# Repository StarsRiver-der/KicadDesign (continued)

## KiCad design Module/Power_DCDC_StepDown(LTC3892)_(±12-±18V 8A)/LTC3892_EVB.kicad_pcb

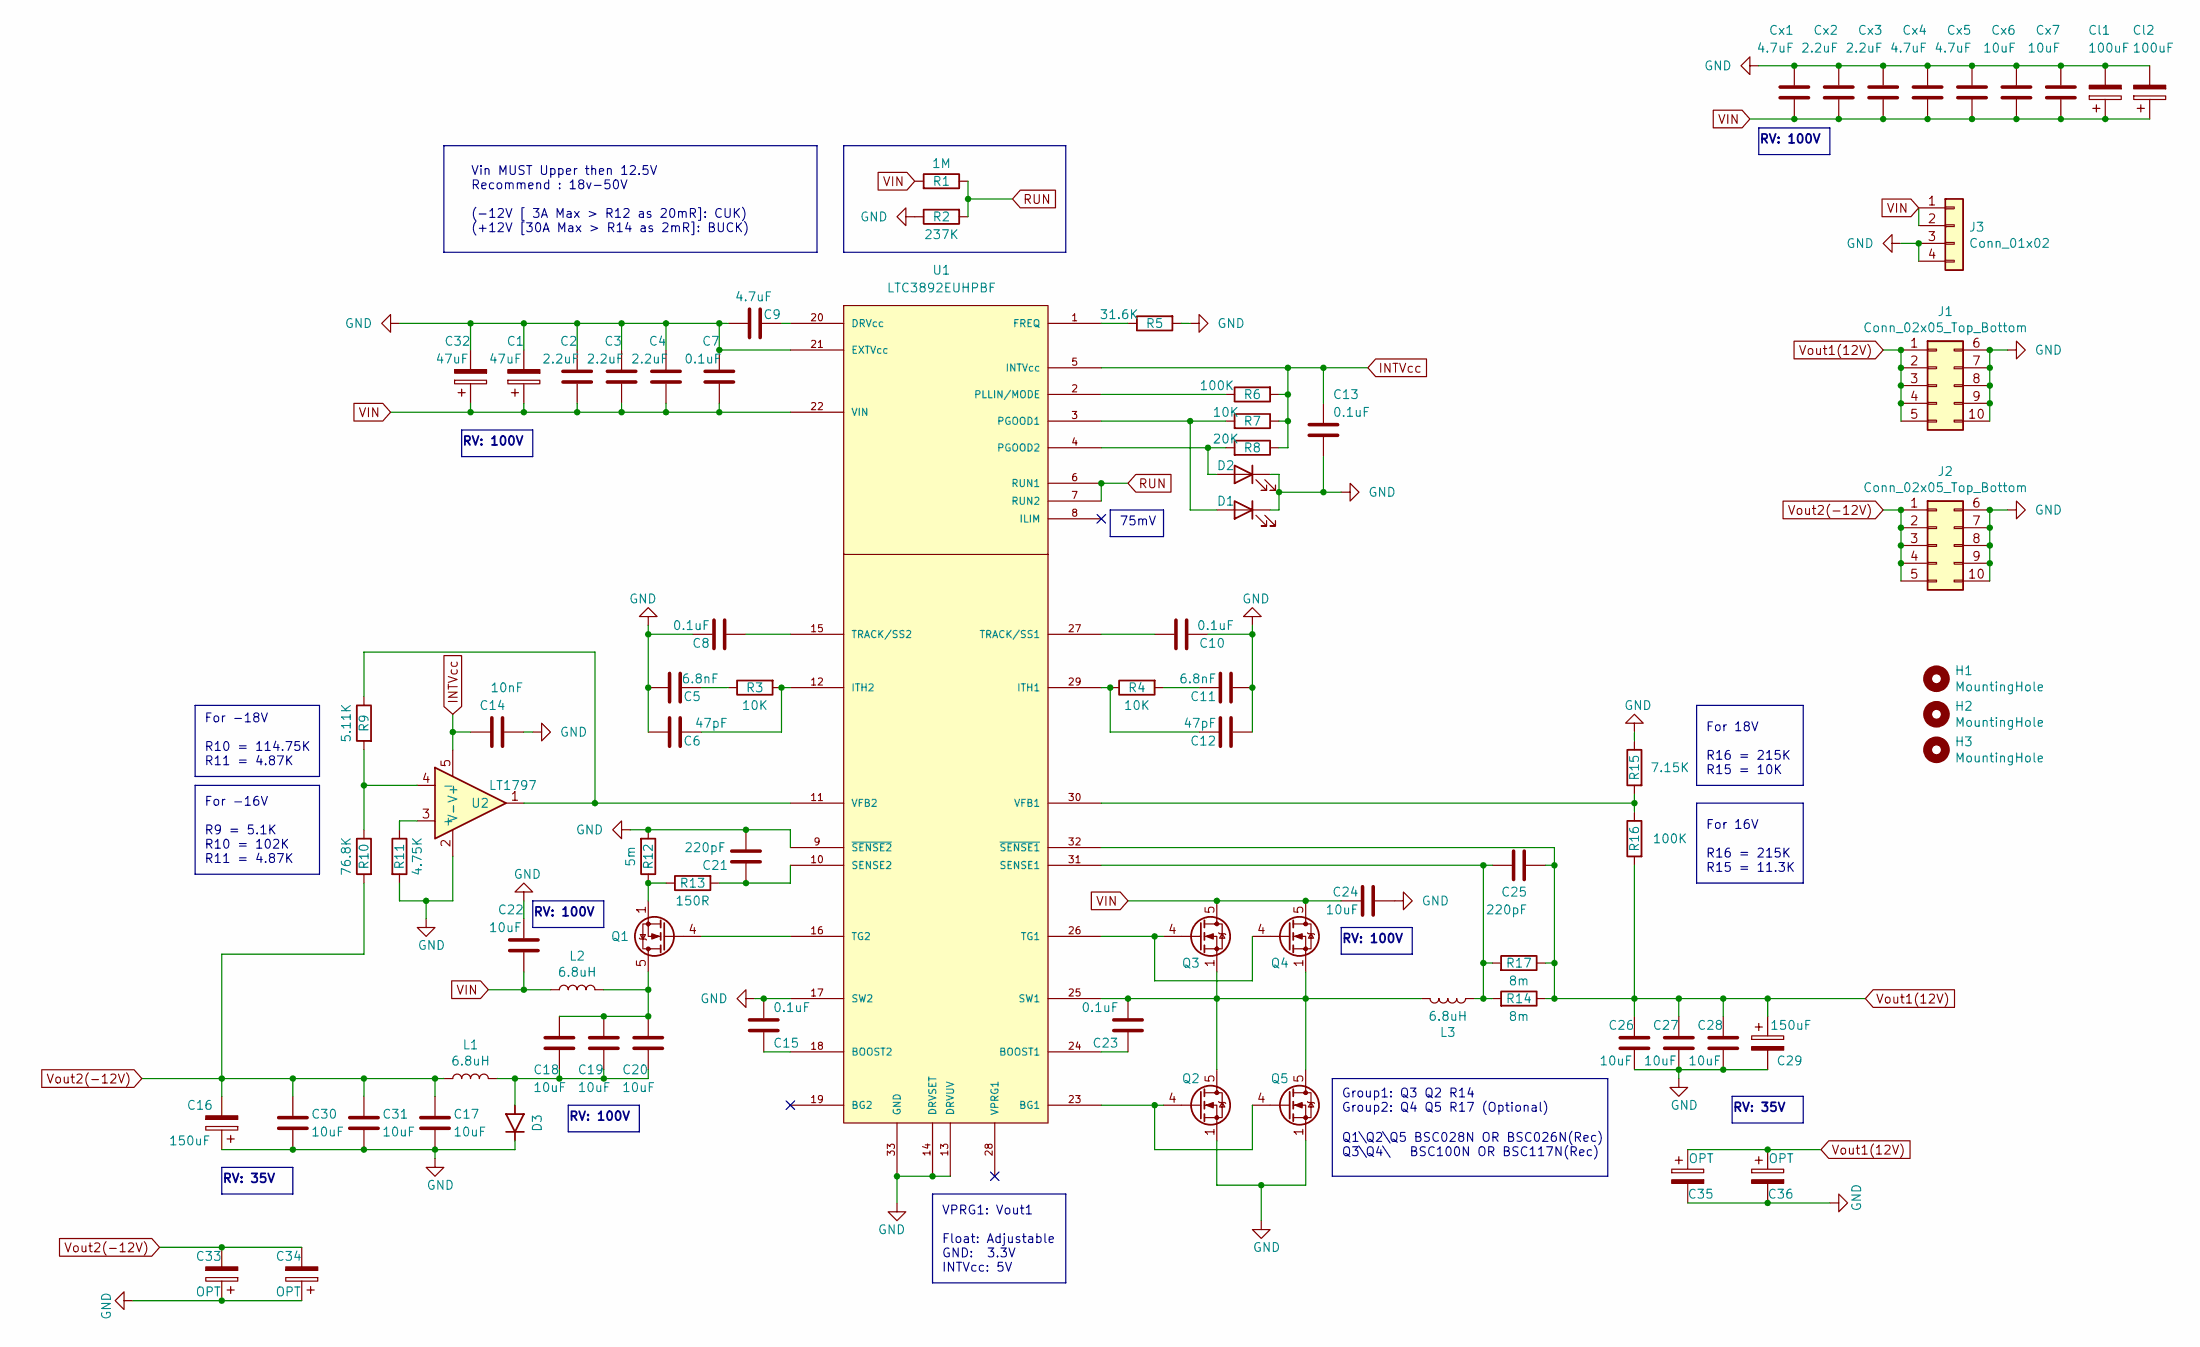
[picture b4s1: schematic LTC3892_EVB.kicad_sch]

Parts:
C1, C32: 47uF; CP_Elec_10x10
C2, C3, C4: 2.2uF; C_1206_3216Metric
C5, C11: 6.8nF; C_0402_1005Metric
C6, C12: 47pF; C_0402_1005Metric
C7, C23: 0.1uF; C_0603_1608Metric
C8, C10, C13, C15: 0.1uF; C_0402_1005Metric
C9: 4.7uF; C_0402_1005Metric
C14: 10nF; C_0402_1005Metric
C16, C29: 150uF; CP_Elec_8x10
C17, C18, C19, C20, C22, C24, C26, C27, C28, C30, C31: 10uF; C_1206_3216Metric
C21, C25: 220pF; C_0402_1005Metric
C33, C34, C35, C36: OPT; CP_Elec_8x10
Cl1, Cl2: 100uF; CP_Elec_10x10
Cx1, Cx4, Cx5: 4.7uF; C_1206_3216Metric
Cx2, Cx3: 2.2uF; C_1206_3216Metric
Cx6, Cx7: 10uF; C_1206_3216Metric
D1, D2: LED; LED_0402_1005Metric
D3: SBR8U60P5-13; DIO_PDS360-13; MPN SBR8U60P5-13
H1, H2, H3: MountingHole; MountingHole_2.2mm_M2
J1, J2: Conn_02x05_Top_Bottom; Molex_Micro-Fit_3.0_43045-1012_2x05_P3.00mm_Vertical
J3: Conn_01x02; Molex_Mini-Fit_Jr_5566-04A_2x02_P4.20mm_Vertical
L1, L2, L3: 6.8uH; L_Wuerth_HCM-1350
Q1, Q2, Q5: BSC026N08NS5; TDSON-8-1
Q3, Q4: BSC117N08NS5; TDSON-8-1
R1: 1M; R_0402_1005Metric
R2: 237K; R_0402_1005Metric
R3, R4, R7: 10K; R_0402_1005Metric
R5: 31.6K; R_0402_1005Metric
R6, R16: 100K; R_0402_1005Metric
R8: 20K; R_0402_1005Metric
R9: 5.11K; R_0402_1005Metric
R10: 76.8K; R_0402_1005Metric
R11: 4.75K; R_0402_1005Metric
R12: 5m; R_2512_6332Metric
R13: 150R; R_0402_1005Metric
R14, R17: 8m; R_2512_6332Metric
R15: 7.15K; R_0402_1005Metric
U1: LTC3892EUHPBF; QFN-32_UH; MANUFACTURER_PART_NUMBER ltc3892euh#pbf
U2: LT1797; SOT-23-5

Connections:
GND: C1.2, C2.2, C3.2, C4.2, C5.1, C6.1, C7.2, C8.1, C9.1, C10.2, C11.2, C12.2, C13.2, C14.2, C15.1, C16.1, C17.1, C21.1, C22.2, C24.2, C26.1, C27.1, C28.1, C29.2, C30.1, C31.1, C32.2, C33.1, C34.1, C35.2, C36.2, Cl1.2, Cl2.2, Cx1.1, Cx2.1, Cx3.1, Cx4.1, Cx5.1, Cx6.1, Cx7.1, D1.1 (K), D2.1 (K), D3.3, J1.6, J1.7, J1.8, J1.9, J1.10, J2.6, J2.7, J2.8, J2.9, J2.10, J3.3, J3.4, Q2.1 (S), Q2.2 (S), Q2.3 (S), Q5.1 (S), Q5.2 (S), Q5.3 (S), R2.1, R5.2, R11.2, R12.2, R15.1, U1.9 (~SENSE2), U1.13 (DRVUV), U1.14 (DRVSET), U1.17 (SW2), U1.21 (EXTVcc), U1.33 (GND), U2.2 (V-)
INTVcc: C13.1, C14.1, R6.2, R7.1, R8.1, U1.5 (INTVcc), U2.5 (V+)
unnamed: C5.2, R3.1
unnamed: C6.2, R3.2, U1.12 (ITH2)
unnamed: C8.2, U1.15 (TRACK/SS2)
unnamed: C9.2, U1.20 (DRVcc)
unnamed: C10.1, U1.27 (TRACK/SS1)
unnamed: C11.1, R4.2
unnamed: C12.1, R4.1, U1.29 (ITH1)
unnamed: C15.2, U1.18 (BOOST2)
unnamed: C18.1, C19.1, C20.1, D3.1, D3.2, L1.2
unnamed: C18.2, C19.2, C20.2, L2.2, Q1.5 (D)
unnamed: C21.2, R13.2, U1.10 (SENSE2)
unnamed: C23.1, L3.1, Q2.5 (D), Q3.1 (S), Q3.2 (S), Q3.3 (S), Q4.1 (S), Q4.2 (S), Q4.3 (S), Q5.5 (D), U1.25 (SW1)
unnamed: C23.2, U1.24 (BOOST1)
unnamed: C25.1, L3.2, R14.2, R17.2, U1.31 (SENSE1)
unnamed: D1.2 (A), R7.2, U1.3 (PGOOD1)
unnamed: D2.2 (A), R8.2, U1.4 (PGOOD2)
unnamed: Q1.1 (S), Q1.2 (S), Q1.3 (S), R12.1, R13.1
unnamed: Q1.4 (G), U1.16 (TG2)
unnamed: Q2.4 (G), Q5.4 (G), U1.23 (BG1)
unnamed: Q3.4 (G), Q4.4 (G), U1.26 (TG1)
unnamed: R5.1, U1.1 (FREQ)
unnamed: R6.1, U1.2 (PLLIN/MODE)
unnamed: R9.1, U1.11 (VFB2), U2.1
unnamed: R9.2, R10.1, U2.4 (-)
unnamed: R11.1, U2.3 (+)
unnamed: R15.2, R16.1, U1.30 (VFB1)
RUN: R1.1, R2.2, U1.6 (RUN1), U1.7 (RUN2)
VIN: C1.1, C2.1, C3.1, C4.1, C7.1, C22.1, C24.1, C32.1, Cl1.1, Cl2.1, Cx1.2, Cx2.2, Cx3.2, Cx4.2, Cx5.2, Cx6.2, Cx7.2, J3.1, J3.2, L2.1, Q3.5 (D), Q4.5 (D), R1.2, U1.22 (VIN)
Vout1(12V): C25.2, C26.2, C27.2, C28.2, C29.1, C35.1, C36.1, J1.1, J1.2, J1.3, J1.4, J1.5, R14.1, R16.2, R17.1, U1.32 (~SENSE1)
Vout2(-12V): C16.2, C17.2, C30.2, C31.2, C33.2, C34.2, J2.1, J2.2, J2.3, J2.4, J2.5, L1.1, R10.2

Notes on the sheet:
For 18V R16 = 215K R15 = 10K
For -18V R10 = 114.75K R11 = 4.87K
Vin MUST Upper then 12.5V Recommend : 18v-50V (-12V [ 3A Max > R12 as 20mR]: CUK) (+12V [30A Max > R14 as 2mR]: BUCK)
RV: 100V
RV: 35V
For -16V R9 = 5.1K R10 = 102K R11 = 4.87K
Q1\Q2\Q5 BSC028N OR BSC026N(Rec) Q3\Q4\ BSC100N OR BSC117N(Rec)
75mV
VPRG1: Vout1 Float: Adjustable GND: 3.3V INTVcc: 5V
Group1: Q3 Q2 R14 Group2: Q4 Q5 R17 (Optional)
For 16V R16 = 215K R15 = 11.3K

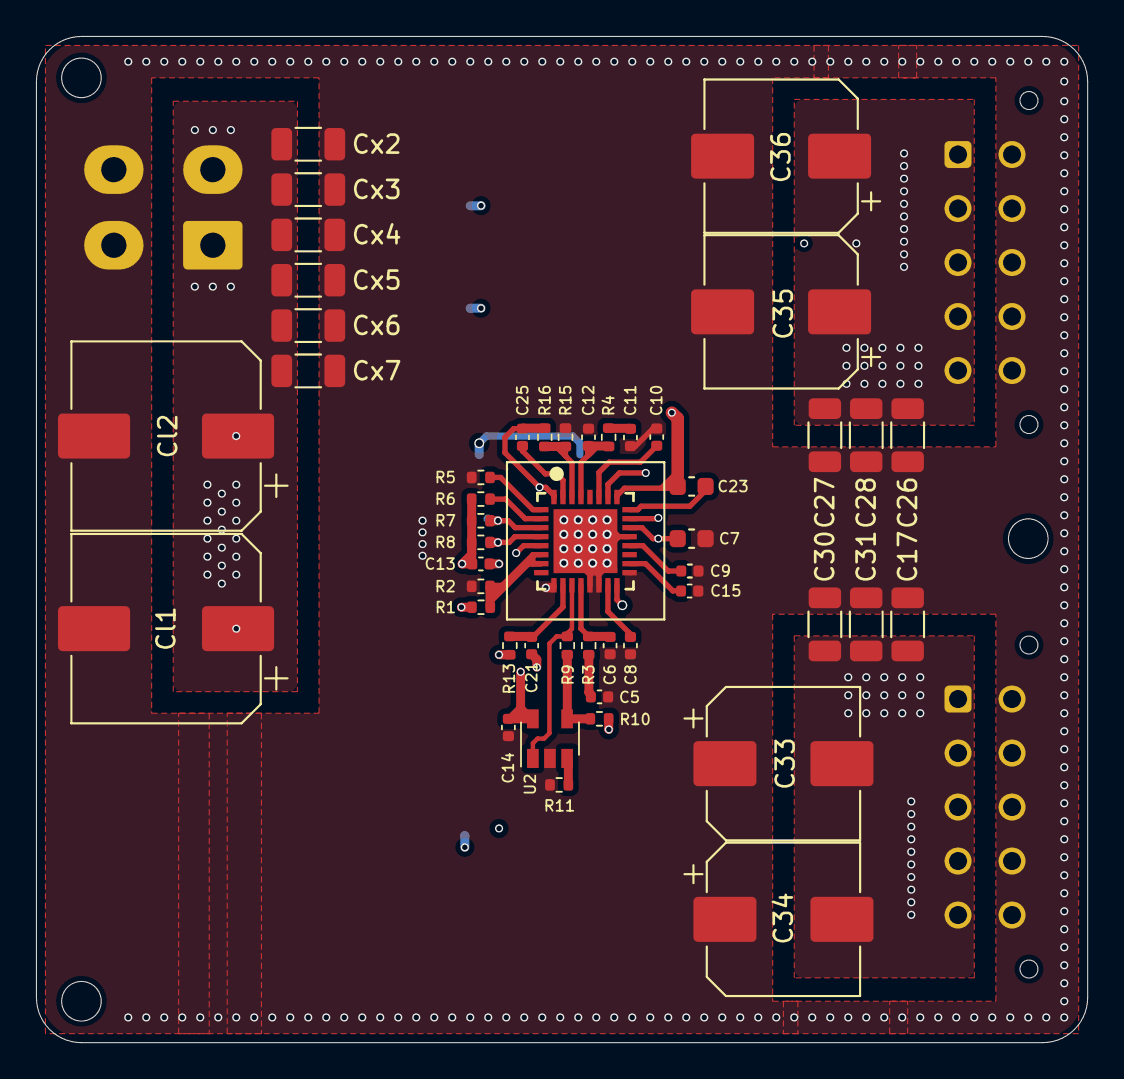
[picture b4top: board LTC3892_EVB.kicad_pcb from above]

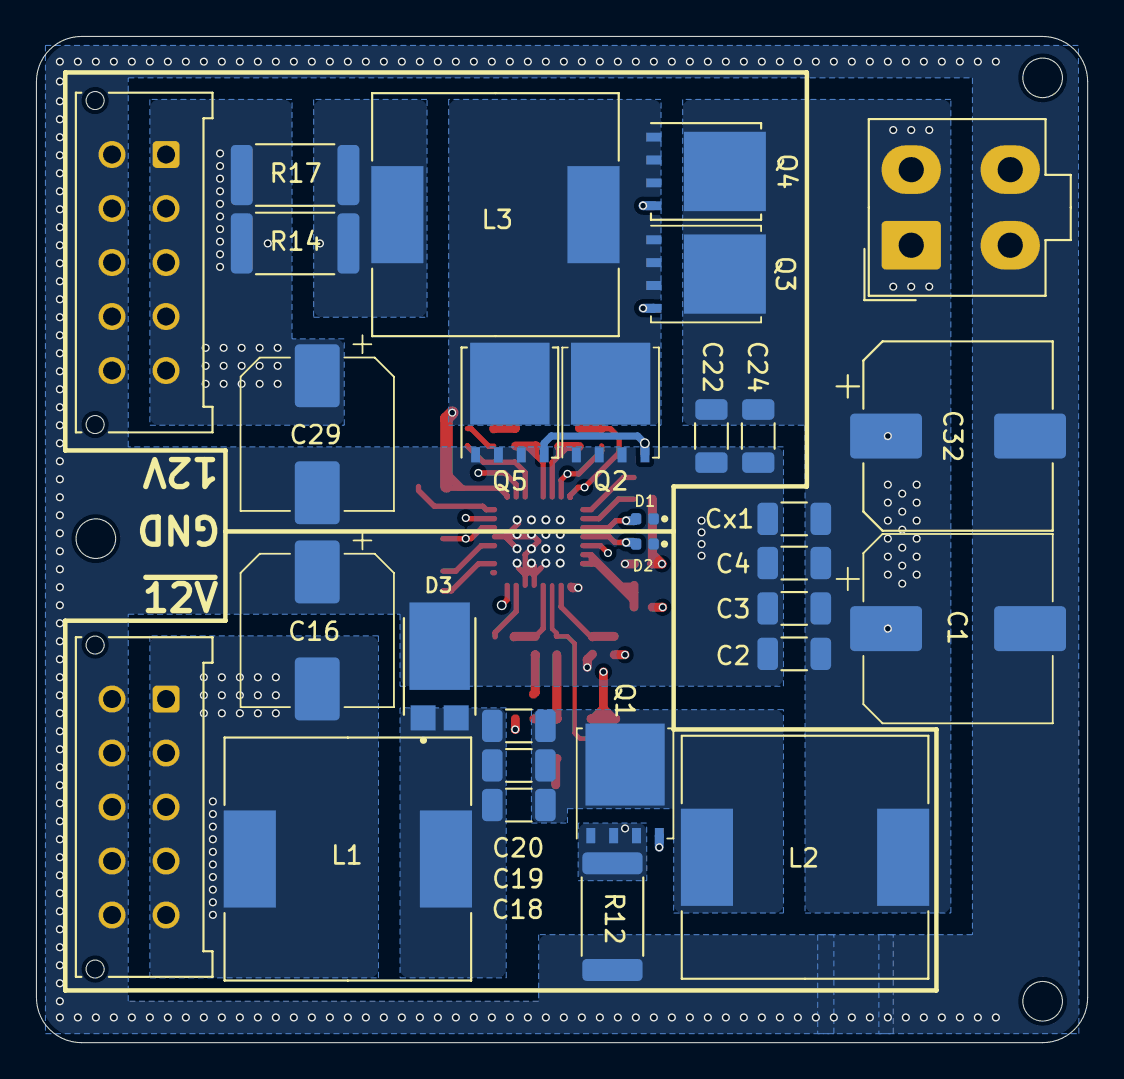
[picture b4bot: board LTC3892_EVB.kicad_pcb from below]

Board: 4 copper layers, 58.4 x 55.9 mm, 81 parts (30 on the bottom side), 32 nets.

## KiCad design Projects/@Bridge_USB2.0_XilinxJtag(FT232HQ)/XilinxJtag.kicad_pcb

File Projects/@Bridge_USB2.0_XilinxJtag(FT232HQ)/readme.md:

# XIlinx Jtag编程器
为ISE和Vivado适配

# 预览

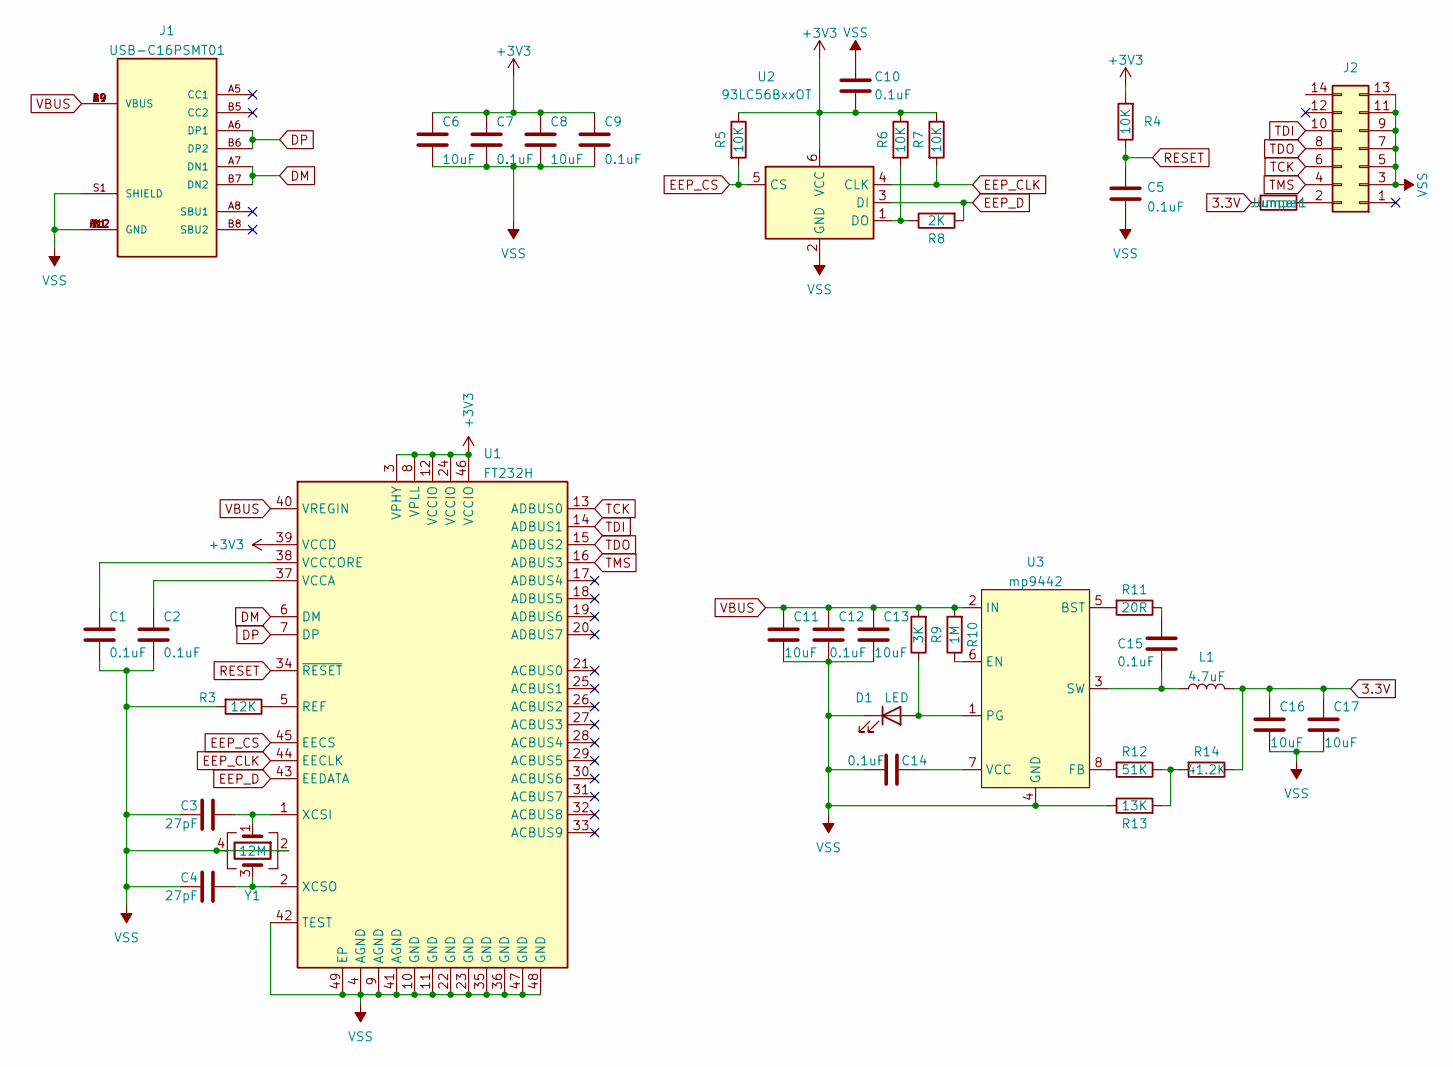
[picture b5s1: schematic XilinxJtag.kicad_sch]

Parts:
C1, C2, C5, C7, C9, C10, C12, C14, C15: 0.1uF; C_0402_1005Metric
C3, C4: 27pF; C_0402_1005Metric
C6, C8, C11, C13, C16, C17: 10uF; C_0402_1005Metric
D1: LED; LED_0402_1005Metric
J1: USB-C16PSMT01; USB_C_Receptacle_XKB_U262-16XN-4BVC11; PARTREV A
J2: Conn_01x06_Male; PinHeader_2x07_P2.54mm_Vertical
Jumper1: Jumper; R_0402_1005Metric
L1: 4.7uF; L_Taiyo-Yuden_NR-30xx
R3: 12K; R_0402_1005Metric
R4, R5, R6, R7: 10K; R_0402_1005Metric
R8: 2K; R_0402_1005Metric
R9: 3K; R_0402_1005Metric
R10: 1M; R_0402_1005Metric
R11: 20R; R_0402_1005Metric
R12: 51K; R_0402_1005Metric
R13: 13K; R_0402_1005Metric
R14: 41.2K; R_0402_1005Metric
U1: FT232H; QFN-48-1EP_8x8mm_P0.5mm_EP6.2x6.2mm
U2: 93LC56BxxOT; SOT-23-6
U3: mp9442; TSOT-23-8
Y1: 12M; Crystal_SMD_2016-4Pin_2.0x1.6mm

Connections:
3.3V: C16.1, C17.1, Jumper1.2, L1.2, R14.1
+3V3: C6.1, C7.1, C8.1, C9.1, C10.1, R4.2, R5.1, R6.1, R7.1, U1.3 (VPHY), U1.8 (VPLL), U1.12 (VCCIO), U1.24 (VCCIO), U1.39 (VCCD), U1.46 (VCCIO), U2.6 (VCC)
DM: J1.A7 (DN1), J1.B7 (DN2), U1.6 (DM)
DP: J1.A6 (DP1), J1.B6 (DP2), U1.7 (DP)
EEP_CLK: R7.2, U1.44 (EECLK), U2.4 (CLK)
EEP_CS: R5.2, U1.45 (EECS), U2.5 (CS)
EEP_D: R8.2, U1.43 (EEDATA), U2.3 (DI)
unnamed: C1.1, U1.38 (VCCCORE)
unnamed: C2.1, U1.37 (VCCA)
unnamed: C3.2, U1.1 (XCSI), Y1.1
unnamed: C4.2, U1.2 (XCSO), Y1.3
unnamed: C14.1, U3.7 (VCC)
unnamed: C15.1, R11.1
unnamed: C15.2, L1.1, U3.3 (SW)
unnamed: D1.2 (A), R9.1, U3.1 (PG)
unnamed: J2.2, Jumper1.1
unnamed: R3.1, U1.5 (REF)
unnamed: R6.2, R8.1, U2.1 (DO)
unnamed: R10.1, U3.6 (EN)
unnamed: R11.2, U3.5 (BST)
unnamed: R12.1, R13.2, R14.2
unnamed: R12.2, U3.8 (FB)
RESET: C5.1, R4.1, U1.34 (~RESET)
TCK: J2.6, U1.13 (ADBUS0)
TDI: J2.10, U1.14 (ADBUS1)
TDO: J2.8, U1.15 (ADBUS2)
TMS: J2.4, U1.16 (ADBUS3)
VBUS: C11.1, C12.1, C13.1, J1.A4 (VBUS), J1.A9 (VBUS), J1.B4 (VBUS), J1.B9 (VBUS), R9.2, R10.2, U1.40 (VREGIN), U3.2 (IN)
VSS: C1.2, C2.2, C3.1, C4.1, C5.2, C6.2, C7.2, C8.2, C9.2, C10.2, C11.2, C12.2, C13.2, C14.2, C16.2, C17.2, D1.1 (K), J1.A1 (GND), J1.A12 (GND), J1.B1 (GND), J1.B12 (GND), J1.S1 (SHIELD), J2.3, J2.5, J2.7, J2.9, J2.11, J2.13, R3.2, R13.1, U1.4 (AGND), U1.9 (AGND), U1.10 (GND), U1.11 (GND), U1.22 (GND), U1.23 (GND), U1.35 (GND), U1.36 (GND), U1.41 (AGND), U1.42 (TEST), U1.47 (GND), U1.48 (GND), U1.49 (EP), U2.2 (GND), U3.4 (GND), Y1.2, Y1.4

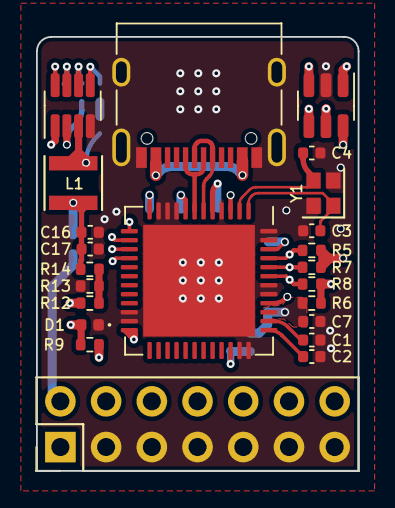
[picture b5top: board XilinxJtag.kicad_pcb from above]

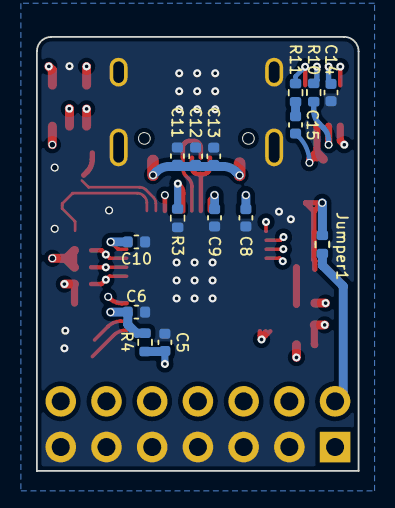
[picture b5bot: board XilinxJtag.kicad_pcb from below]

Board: 4 copper layers, 17.9 x 24.1 mm, 38 parts (15 on the bottom side), 29 nets.

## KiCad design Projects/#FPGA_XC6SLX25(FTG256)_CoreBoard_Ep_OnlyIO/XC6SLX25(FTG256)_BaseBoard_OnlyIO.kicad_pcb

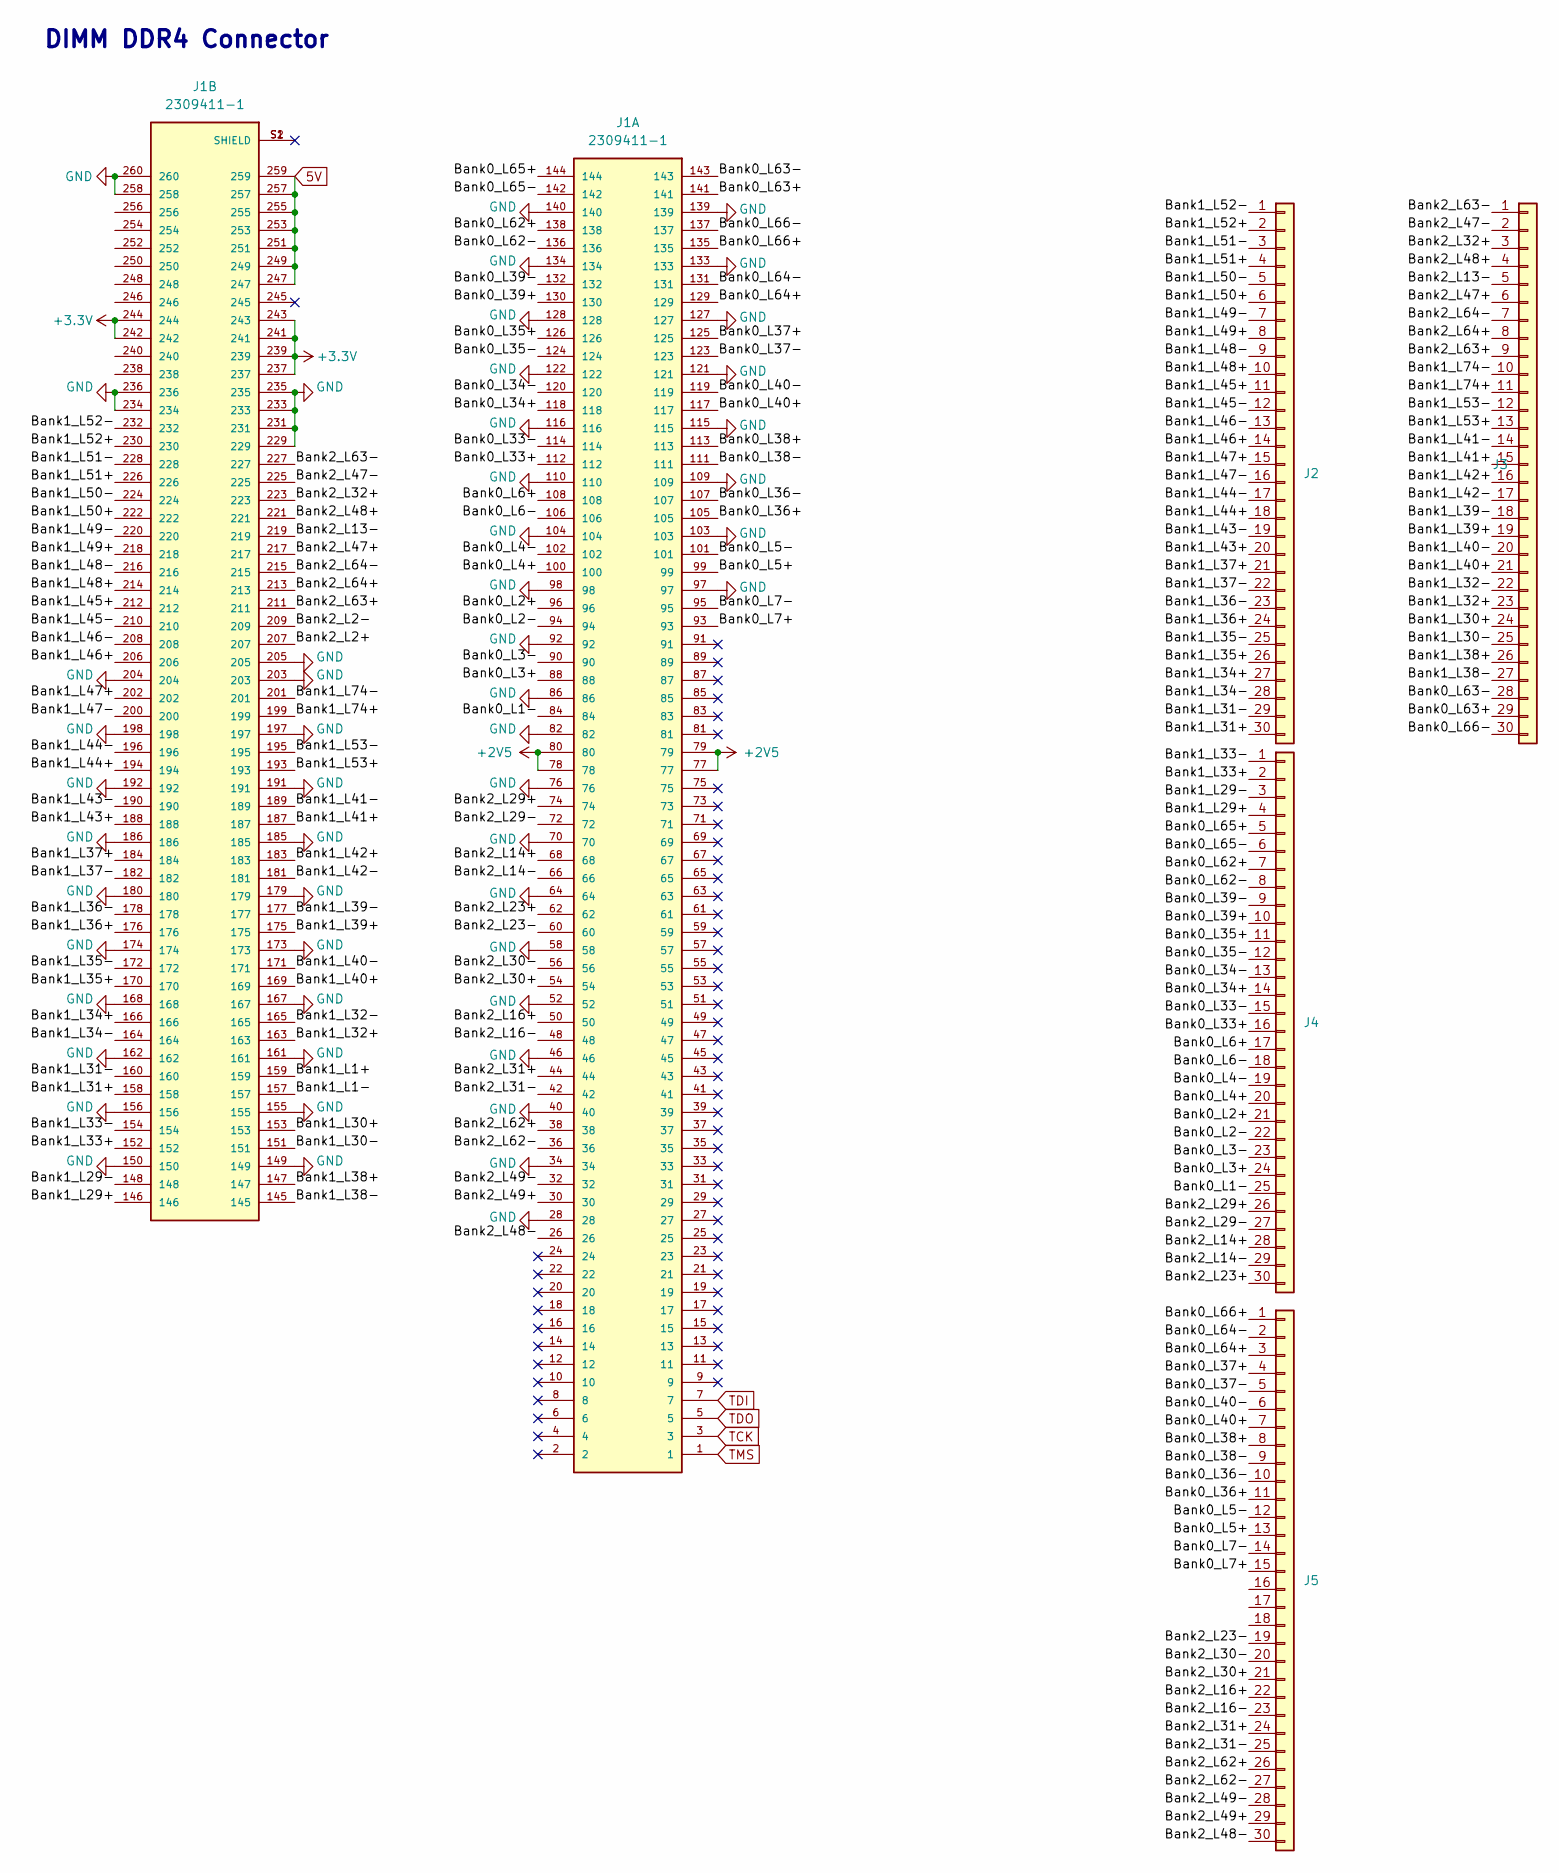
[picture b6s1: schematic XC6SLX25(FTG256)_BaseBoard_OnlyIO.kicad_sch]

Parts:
J1: 2309411-1; SO-DIMM-DDR4-slot-2309408-r
J2, J3, J4, J5: Conn_01x30; PinSocket_1x30_P2.54mm_Vertical

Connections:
5V: J1.247, J1.249, J1.251, J1.253, J1.255, J1.257, J1.259
+2V5: J1.77, J1.78, J1.79, J1.80
+3V3: J1.237, J1.239, J1.241, J1.242, J1.243, J1.244
/Bank0_L1-: J1.84, J4.25
/Bank0_L2+: J1.96, J4.21
/Bank0_L2-: J1.94, J4.22
/Bank0_L3+: J1.88, J4.24
/Bank0_L3-: J1.90, J4.23
/Bank0_L4+: J1.100, J4.20
/Bank0_L4-: J1.102, J4.19
/Bank0_L5+: J1.99, J5.13
/Bank0_L5-: J1.101, J5.12
/Bank0_L6+: J1.108, J4.17
/Bank0_L6-: J1.106, J4.18
/Bank0_L7+: J1.93, J5.15
/Bank0_L7-: J1.95, J5.14
/Bank0_L33+: J1.112, J4.16
/Bank0_L33-: J1.114, J4.15
/Bank0_L34+: J1.118, J4.14
/Bank0_L34-: J1.120, J4.13
/Bank0_L35+: J1.126, J4.11
/Bank0_L35-: J1.124, J4.12
/Bank0_L36+: J1.105, J5.11
/Bank0_L36-: J1.107, J5.10
/Bank0_L37+: J1.125, J5.4
/Bank0_L37-: J1.123, J5.5
/Bank0_L38+: J1.113, J5.8
/Bank0_L38-: J1.111, J5.9
/Bank0_L39+: J1.130, J4.10
/Bank0_L39-: J1.132, J4.9
/Bank0_L40+: J1.117, J5.7
/Bank0_L40-: J1.119, J5.6
/Bank0_L62+: J1.138, J4.7
/Bank0_L62-: J1.136, J4.8
/Bank0_L63+: J1.141, J3.29
/Bank0_L63-: J1.143, J3.28
/Bank0_L64+: J1.129, J5.3
/Bank0_L64-: J1.131, J5.2
/Bank0_L65+: J1.144, J4.5
/Bank0_L65-: J1.142, J4.6
/Bank0_L66+: J1.135, J5.1
/Bank0_L66-: J1.137, J3.30
/Bank1_L1+: J1.159
/Bank1_L1-: J1.157
/Bank1_L29+: J1.146, J4.4
/Bank1_L29-: J1.148, J4.3
/Bank1_L30+: J1.153, J3.24
/Bank1_L30-: J1.151, J3.25
/Bank1_L31+: J1.158, J2.30
/Bank1_L31-: J1.160, J2.29
/Bank1_L32+: J1.163, J3.23
/Bank1_L32-: J1.165, J3.22
/Bank1_L33+: J1.152, J4.2
/Bank1_L33-: J1.154, J4.1
/Bank1_L34+: J1.166, J2.27
/Bank1_L34-: J1.164, J2.28
/Bank1_L35+: J1.170, J2.26
/Bank1_L35-: J1.172, J2.25
/Bank1_L36+: J1.176, J2.24
/Bank1_L36-: J1.178, J2.23
/Bank1_L37+: J1.184, J2.21
/Bank1_L37-: J1.182, J2.22
/Bank1_L38+: J1.147, J3.26
/Bank1_L38-: J1.145, J3.27
/Bank1_L39+: J1.175, J3.19
/Bank1_L39-: J1.177, J3.18
/Bank1_L40+: J1.169, J3.21
/Bank1_L40-: J1.171, J3.20
/Bank1_L41+: J1.187, J3.15
/Bank1_L41-: J1.189, J3.14
/Bank1_L42+: J1.183, J3.16
/Bank1_L42-: J1.181, J3.17
/Bank1_L43+: J1.188, J2.20
/Bank1_L43-: J1.190, J2.19
/Bank1_L44+: J1.194, J2.18
/Bank1_L44-: J1.196, J2.17
/Bank1_L45+: J1.212, J2.11
/Bank1_L45-: J1.210, J2.12
/Bank1_L46+: J1.206, J2.14
/Bank1_L46-: J1.208, J2.13
/Bank1_L47+: J1.202, J2.15
/Bank1_L47-: J1.200, J2.16
/Bank1_L48+: J1.214, J2.10
/Bank1_L48-: J1.216, J2.9
/Bank1_L49+: J1.218, J2.8
/Bank1_L49-: J1.220, J2.7
/Bank1_L50+: J1.222, J2.6
/Bank1_L50-: J1.224, J2.5
/Bank1_L51+: J1.226, J2.4
/Bank1_L51-: J1.228, J2.3
/Bank1_L52+: J1.230, J2.2
/Bank1_L52-: J1.232, J2.1
/Bank1_L53+: J1.193, J3.13
/Bank1_L53-: J1.195, J3.12
/Bank1_L74+: J1.199, J3.11
/Bank1_L74-: J1.201, J3.10
/Bank2_L2+: J1.207
/Bank2_L2-: J1.209
/Bank2_L13-: J1.219, J3.5
/Bank2_L14+: J1.68, J4.28
/Bank2_L14-: J1.66, J4.29
/Bank2_L16+: J1.50, J5.22
/Bank2_L16-: J1.48, J5.23
/Bank2_L23+: J1.62, J4.30
/Bank2_L23-: J1.60, J5.19
/Bank2_L29+: J1.74, J4.26
/Bank2_L29-: J1.72, J4.27
/Bank2_L30+: J1.54, J5.21
/Bank2_L30-: J1.56, J5.20
/Bank2_L31+: J1.44, J5.24
/Bank2_L31-: J1.42, J5.25
/Bank2_L32+: J1.223, J3.3
/Bank2_L47+: J1.217, J3.6
/Bank2_L47-: J1.225, J3.2
/Bank2_L48+: J1.221, J3.4
/Bank2_L48-: J1.26, J5.30
/Bank2_L49+: J1.30, J5.29
/Bank2_L49-: J1.32, J5.28
/Bank2_L62+: J1.38, J5.26
/Bank2_L62-: J1.36, J5.27
/Bank2_L63+: J1.211, J3.9
/Bank2_L63-: J1.227, J3.1
/Bank2_L64+: J1.213, J3.8
/Bank2_L64-: J1.215, J3.7
GND: J1.28, J1.34, J1.40, J1.46, J1.52, J1.58, J1.64, J1.70, J1.76, J1.82, J1.86, J1.92, J1.97, J1.98, J1.103, J1.104, J1.109, J1.110, J1.115, J1.116, J1.121, J1.122, J1.127, J1.128, J1.133, J1.134, J1.139, J1.140, J1.149, J1.150, J1.155, J1.156, J1.161, J1.162, J1.167, J1.168, J1.173, J1.174, J1.179, J1.180, J1.185, J1.186, J1.191, J1.192, J1.197, J1.198, J1.203, J1.204, J1.205, J1.229, J1.231, J1.233, J1.234, J1.235, J1.236, J1.258, J1.260
TCK: J1.3
TDI: J1.7
TDO: J1.5
TMS: J1.1

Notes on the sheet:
DIMM DDR4 Connector

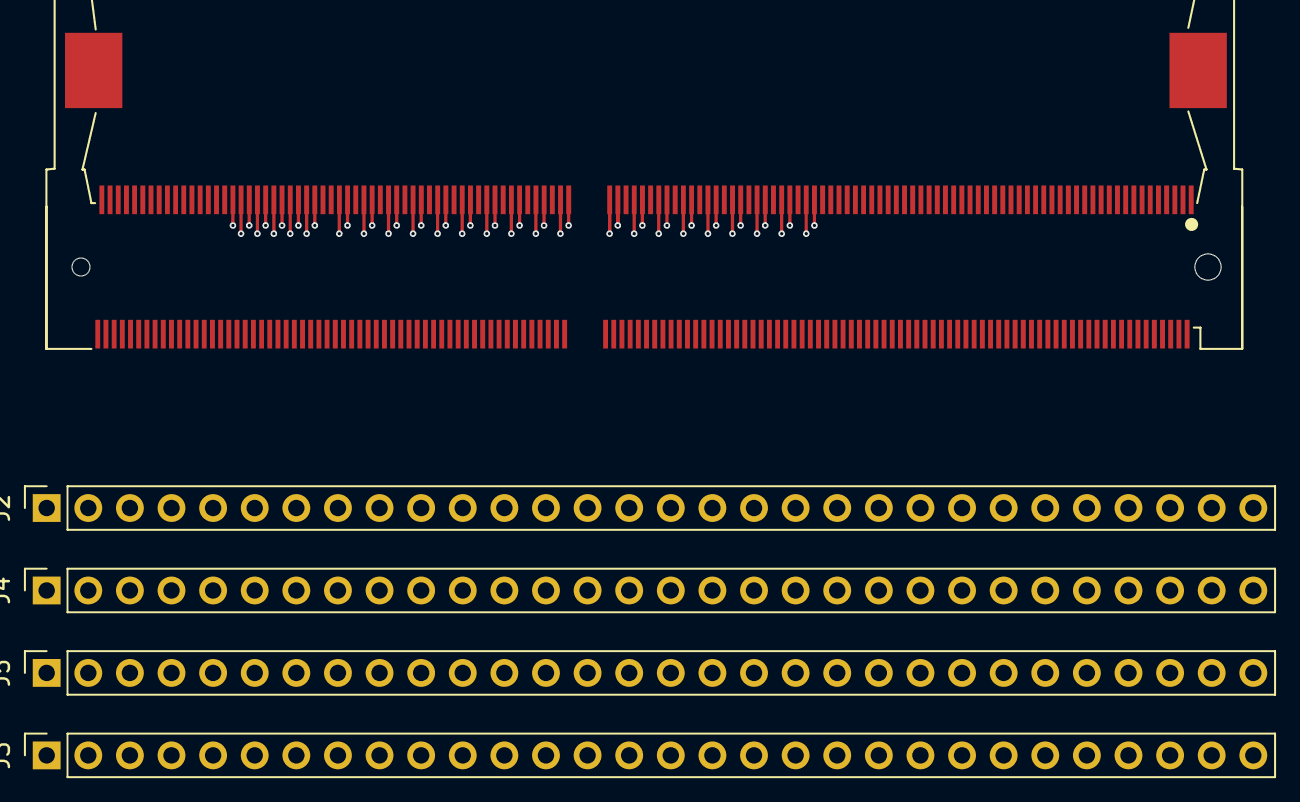
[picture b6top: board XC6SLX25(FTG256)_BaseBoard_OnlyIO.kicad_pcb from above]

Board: 6 copper layers, 5 parts (0 on the bottom side), 121 nets.
